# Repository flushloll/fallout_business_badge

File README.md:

Made in one day during Fallout IRL hackathon.

This business badge features:
36 neopixel leds emulating a display
2 buttons for input and led setting changes
esp32 c3 for managing inputs and controlling leds

## BOM:

<h3><a href="fallout_badge/jlcpcb/production_files/CPL-fallout_badge.csv">BOM CSV</a></h3>

@flush on slack

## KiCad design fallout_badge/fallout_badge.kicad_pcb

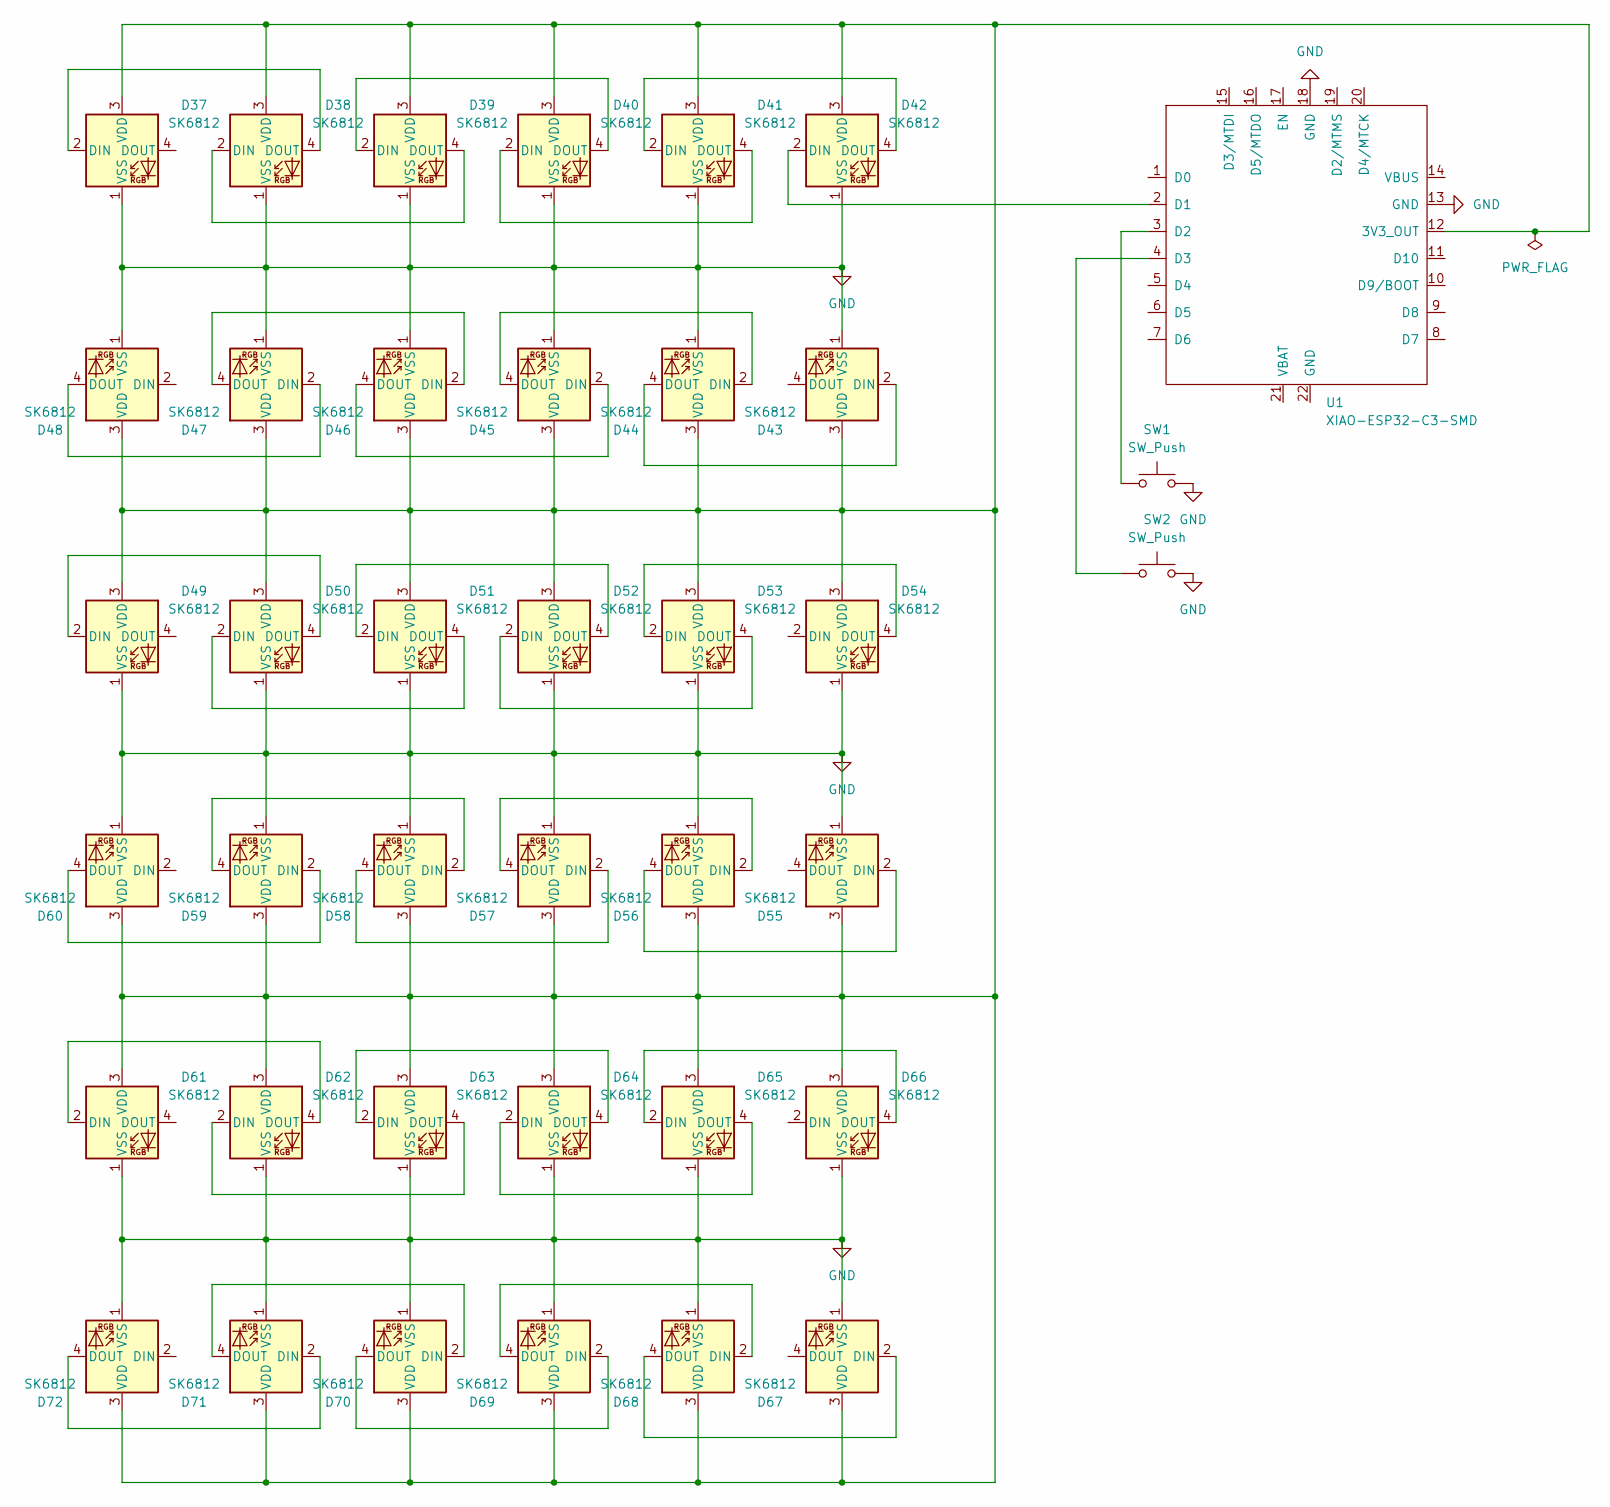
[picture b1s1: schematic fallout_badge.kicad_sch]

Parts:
D37, D38, D39, D40, D41, D42, D43, D44, D45, D46, D47, D48, D49, D50, D51, D52, D53, D54, D55, D56, D57, D58, D59, D60, D61, D62, D63, D64, D65, D66, D67, D68, D69, D70, D71, D72: SK6812; LED_SK6812_PLCC4_5.0x5.0mm_P3.2mm
SW1, SW2: SW_Push; SW_PUSH_6mm
U1: XIAO-ESP32-C3-SMD

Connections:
GND: D37.1 (VSS), D38.1 (VSS), D39.1 (VSS), D40.1 (VSS), D41.1 (VSS), D42.1 (VSS), D43.1 (VSS), D44.1 (VSS), D45.1 (VSS), D46.1 (VSS), D47.1 (VSS), D48.1 (VSS), D49.1 (VSS), D50.1 (VSS), D51.1 (VSS), D52.1 (VSS), D53.1 (VSS), D54.1 (VSS), D55.1 (VSS), D56.1 (VSS), D57.1 (VSS), D58.1 (VSS), D59.1 (VSS), D60.1 (VSS), D61.1 (VSS), D62.1 (VSS), D63.1 (VSS), D64.1 (VSS), D65.1 (VSS), D66.1 (VSS), D67.1 (VSS), D68.1 (VSS), D69.1 (VSS), D70.1 (VSS), D71.1 (VSS), D72.1 (VSS), SW1.2, SW2.2, U1.13 (GND), U1.18 (GND)
unnamed: D37.2 (DIN), D38.4 (DOUT)
unnamed: D37.3 (VDD), D38.3 (VDD), D39.3 (VDD), D40.3 (VDD), D41.3 (VDD), D42.3 (VDD), D43.3 (VDD), D44.3 (VDD), D45.3 (VDD), D46.3 (VDD), D47.3 (VDD), D48.3 (VDD), D49.3 (VDD), D50.3 (VDD), D51.3 (VDD), D52.3 (VDD), D53.3 (VDD), D54.3 (VDD), D55.3 (VDD), D56.3 (VDD), D57.3 (VDD), D58.3 (VDD), D59.3 (VDD), D60.3 (VDD), D61.3 (VDD), D62.3 (VDD), D63.3 (VDD), D64.3 (VDD), D65.3 (VDD), D66.3 (VDD), D67.3 (VDD), D68.3 (VDD), D69.3 (VDD), D70.3 (VDD), D71.3 (VDD), D72.3 (VDD), U1.12 (3V3_OUT)
unnamed: D38.2 (DIN), D39.4 (DOUT)
unnamed: D39.2 (DIN), D40.4 (DOUT)
unnamed: D40.2 (DIN), D41.4 (DOUT)
unnamed: D41.2 (DIN), D42.4 (DOUT)
unnamed: D42.2 (DIN), U1.2 (D1)
unnamed: D43.2 (DIN), D44.4 (DOUT)
unnamed: D44.2 (DIN), D45.4 (DOUT)
unnamed: D45.2 (DIN), D46.4 (DOUT)
unnamed: D46.2 (DIN), D47.4 (DOUT)
unnamed: D47.2 (DIN), D48.4 (DOUT)
unnamed: D49.2 (DIN), D50.4 (DOUT)
unnamed: D50.2 (DIN), D51.4 (DOUT)
unnamed: D51.2 (DIN), D52.4 (DOUT)
unnamed: D52.2 (DIN), D53.4 (DOUT)
unnamed: D53.2 (DIN), D54.4 (DOUT)
unnamed: D55.2 (DIN), D56.4 (DOUT)
unnamed: D56.2 (DIN), D57.4 (DOUT)
unnamed: D57.2 (DIN), D58.4 (DOUT)
unnamed: D58.2 (DIN), D59.4 (DOUT)
unnamed: D59.2 (DIN), D60.4 (DOUT)
unnamed: D61.2 (DIN), D62.4 (DOUT)
unnamed: D62.2 (DIN), D63.4 (DOUT)
unnamed: D63.2 (DIN), D64.4 (DOUT)
unnamed: D64.2 (DIN), D65.4 (DOUT)
unnamed: D65.2 (DIN), D66.4 (DOUT)
unnamed: D67.2 (DIN), D68.4 (DOUT)
unnamed: D68.2 (DIN), D69.4 (DOUT)
unnamed: D69.2 (DIN), D70.4 (DOUT)
unnamed: D70.2 (DIN), D71.4 (DOUT)
unnamed: D71.2 (DIN), D72.4 (DOUT)
unnamed: SW1.1, U1.3 (D2)
unnamed: SW2.1, U1.4 (D3)

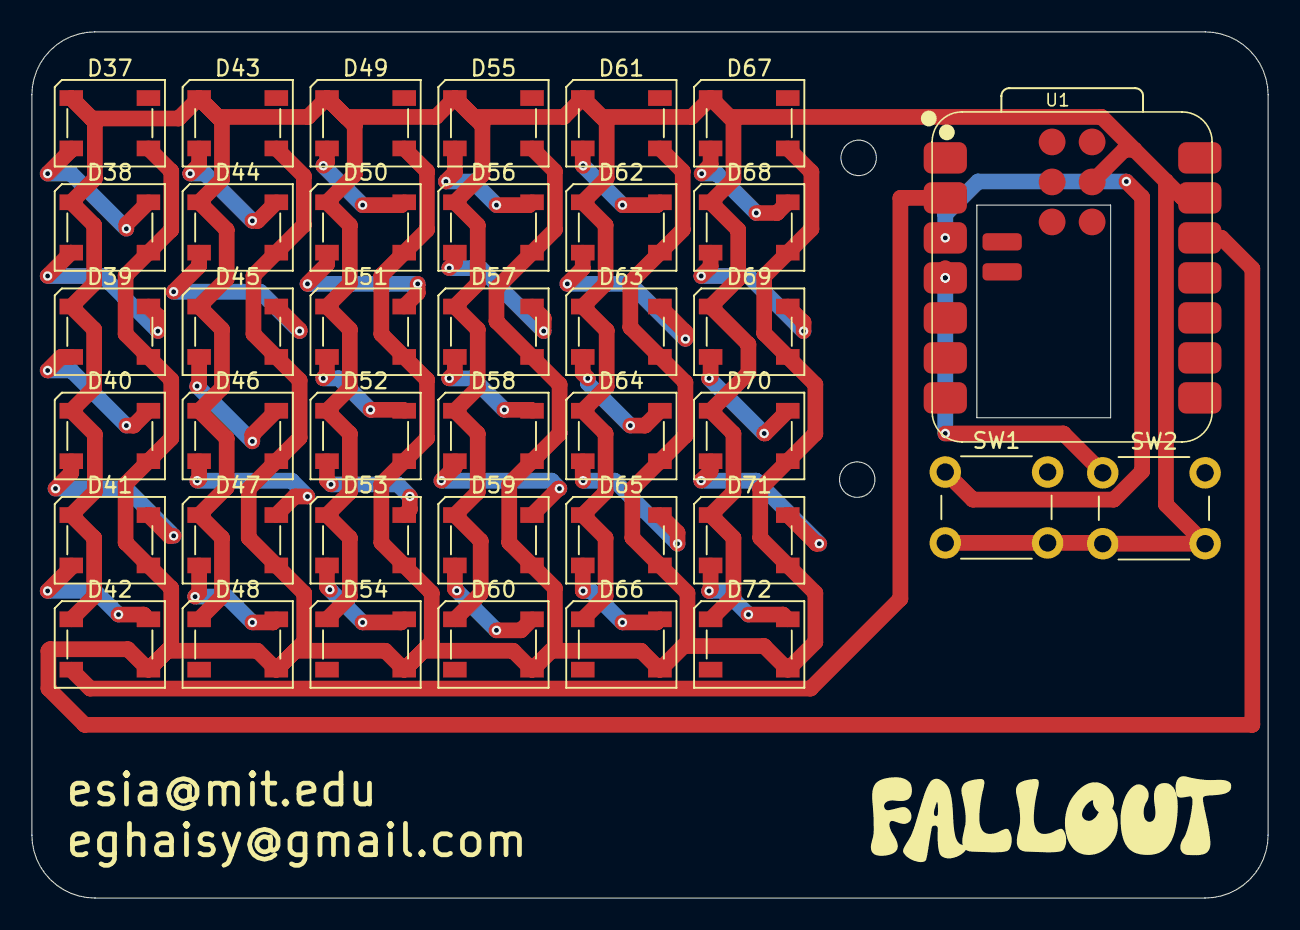
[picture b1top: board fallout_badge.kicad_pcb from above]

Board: 2 copper layers, 78.5 x 55.0 mm, 39 parts (0 on the bottom side), 35 nets.

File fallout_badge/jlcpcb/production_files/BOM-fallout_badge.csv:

Comment,Designator,Footprint,LCSC,Quantity
XIAO-ESP32-C3-SMD,U1,XIAO-ESP32-C3-SMD,,1
SW_Push,SW2,SW_PUSH_6mm,,1
SW_Push,SW1,SW_PUSH_6mm,,1
SK6812,D72,LED_SK6812_PLCC4_5.0x5.0mm_P3.2mm,,1
SK6812,D71,LED_SK6812_PLCC4_5.0x5.0mm_P3.2mm,,1
SK6812,D70,LED_SK6812_PLCC4_5.0x5.0mm_P3.2mm,,1
SK6812,D69,LED_SK6812_PLCC4_5.0x5.0mm_P3.2mm,,1
SK6812,D68,LED_SK6812_PLCC4_5.0x5.0mm_P3.2mm,,1
SK6812,D67,LED_SK6812_PLCC4_5.0x5.0mm_P3.2mm,,1
SK6812,D66,LED_SK6812_PLCC4_5.0x5.0mm_P3.2mm,,1
SK6812,D65,LED_SK6812_PLCC4_5.0x5.0mm_P3.2mm,,1
SK6812,D64,LED_SK6812_PLCC4_5.0x5.0mm_P3.2mm,,1
SK6812,D63,LED_SK6812_PLCC4_5.0x5.0mm_P3.2mm,,1
SK6812,D62,LED_SK6812_PLCC4_5.0x5.0mm_P3.2mm,,1
SK6812,D61,LED_SK6812_PLCC4_5.0x5.0mm_P3.2mm,,1
SK6812,D60,LED_SK6812_PLCC4_5.0x5.0mm_P3.2mm,,1
SK6812,D59,LED_SK6812_PLCC4_5.0x5.0mm_P3.2mm,,1
SK6812,D58,LED_SK6812_PLCC4_5.0x5.0mm_P3.2mm,,1
SK6812,D57,LED_SK6812_PLCC4_5.0x5.0mm_P3.2mm,,1
SK6812,D56,LED_SK6812_PLCC4_5.0x5.0mm_P3.2mm,,1
SK6812,D55,LED_SK6812_PLCC4_5.0x5.0mm_P3.2mm,,1
SK6812,D54,LED_SK6812_PLCC4_5.0x5.0mm_P3.2mm,,1
SK6812,D53,LED_SK6812_PLCC4_5.0x5.0mm_P3.2mm,,1
SK6812,D52,LED_SK6812_PLCC4_5.0x5.0mm_P3.2mm,,1
SK6812,D51,LED_SK6812_PLCC4_5.0x5.0mm_P3.2mm,,1
SK6812,D50,LED_SK6812_PLCC4_5.0x5.0mm_P3.2mm,,1
SK6812,D49,LED_SK6812_PLCC4_5.0x5.0mm_P3.2mm,,1
SK6812,D48,LED_SK6812_PLCC4_5.0x5.0mm_P3.2mm,,1
SK6812,D47,LED_SK6812_PLCC4_5.0x5.0mm_P3.2mm,,1
SK6812,D46,LED_SK6812_PLCC4_5.0x5.0mm_P3.2mm,,1
SK6812,D45,LED_SK6812_PLCC4_5.0x5.0mm_P3.2mm,,1
SK6812,D44,LED_SK6812_PLCC4_5.0x5.0mm_P3.2mm,,1
SK6812,D43,LED_SK6812_PLCC4_5.0x5.0mm_P3.2mm,,1
SK6812,D42,LED_SK6812_PLCC4_5.0x5.0mm_P3.2mm,,1
SK6812,D41,LED_SK6812_PLCC4_5.0x5.0mm_P3.2mm,,1
SK6812,D40,LED_SK6812_PLCC4_5.0x5.0mm_P3.2mm,,1
SK6812,D39,LED_SK6812_PLCC4_5.0x5.0mm_P3.2mm,,1
SK6812,D38,LED_SK6812_PLCC4_5.0x5.0mm_P3.2mm,,1
SK6812,D37,LED_SK6812_PLCC4_5.0x5.0mm_P3.2mm,,1
